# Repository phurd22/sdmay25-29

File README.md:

# Atanasoff-Berry Computer with Modern Technology

Developed by ABCm Development Group (formerly SDMAY25-29 Senior Design) under Dr. Alexander Stoytchev, the ABCm is a modern reimagining of the orignal Atanasoff-Berry Computer.

Built by Dr. Atanasoff and Clifford Berry in 1939, the Atanasoff Berry Computer (ABC) was the first digital electronic computer ever built, and the ABCm seeks to recreate the magic of this device using modern technology and design techniques. This repository houses all the final materials of the project including KiCAD projects, microcontroller and Android scripts, and supplemental documentation.

Orignal information regarding the ABCm project can be found on the [Senior Design website](https://sdmay25-29.sd.ece.iastate.edu/).

## Who are we?

The ABCm Development Group spun off from Iowa State University.  During the 2024-2025 academic year, an Electrical and Computer Engineering (ECpE) Senior Design project was proposed by Dr. Alexander Stoytchev to research the ABC and design a modern equivalent in both hardware and software.

The members of the ABCm Development Group are listed in the included [AUTHORS](./AUTHORS) file.

## Licensing

Hardware, including printed circuit board designs, CAD files, and relevant files, is licensed under [CERN-OHL-P v2](https://cern.ch/cern-ohl).

Logo and relevant components are restricted for use by the ABCm Development Group (see [Branding License and Terms](branding/LICENSE)).

All other source files and documentation herein are licensed under MIT License in their respective folders.

## Repo Guide

- The base-2 and base-10 Android punch card apps are under the 'Android Apps' folder.
- ESP32 scripts can be found under 'ESP32 Development'.
- A simulation of the ABC's control panel and Gaussian elimination algorithm are found under 'Java'.
- A simulation of the ABC in Quartus Prime can be found in 'Quartus Prime Projects'.
- A simulation of the ABC in Java can be found under 'abc-emulator'.
- Our KiCad projects are found in the folder 'KiCadProjects'. Note: these weren't used in our final implementation.
- A punch card generating program can be found under 'Decimal to Binary Page Generator'.
- Various notes on the specific modules are under 'Adder-Subtractor' and 'Base Converter'.

## GitHub Action to compile KiCad files

This repo contains an example custom PCB designed in KiCAD 5 with settings appropriate for PCB manufacture and assembly by JLCPCB. It also contains a GitHub workflow that generates the files needed by JLCPCB: gerbers, BOM, & position file. The workflow additionally generates a manual order BOM,  interactive BOM, and PDF export of the schematic. The manual order BOM includes components in the schematic not assembled by JLCPCB, such as board components not available through JLCPCB, enclosure, hardware, etc. The interactive BOM is an html document that assists in identifying component locations on the PCB for manual assembly.

## Setup Repository GitHub Actions Permissions

The workflow requires read/write access to the new repository to execute successfully.

In the new repository navigate to ```Settings```, and open the ```Actions``` > ```General``` page.

In the ```Workflow permissions``` section select ```Read and write permissions```

## New Repository Cleanup

The newly created repository will include the ```Example_Design``` example PCB design from the template repo. Files for this need to be removed and files for the new design need created. This is best done in a local clone of the new repository on your PC.

Using your Git client (Fork, GitHub Desktop, etc.) clone your new repository to a local folder on your PC.

Eventually this file, ```README.md```, should be replaced/updated with details for the new project. Consider keeping the ```Placing Orders``` and ```Failed Workflow Troubleshooting``` sections so instructions for ordering the design and troubleshooting workflow issues are readily available.

Update ```description``` and ```ownership``` entries in ```APM.yml```.

## New KiCAD Project Creation

Open the KiCAD 8 application.

In the KiCAD Project Manager select ```File``` > ```New``` > ```Project```.

In the ```Create New Project``` dialog check the box for ```Create a new directory for the project```. (Missing this step will break the GitHub workflow functionality.)

Navigate to the ```KiCadProjects``` folder under your cloned repository directory, Enter a name for your KiCAD project, and select ```Save```.

## KiCAD Schematic Setup

The GitHub workflow requires additional schematic symbol fields beyond the KiCAD defaults.

In the KiCAD schematic editor (Eeschema) select ```Preferences``` > ```Preferences...```

In the ```Eeschema``` > ```Field Name Templates``` section add the following entries:

- Part No
- Link
- LCSC
- Note

Check the ```URL``` box for the Link field.

This will add the above fields to every new symbol added to the schematic.

Note: These are KiCAD application settings and apply across all projects. If multiple users are contributing to the design, they will each need to apply these settings.

These fields can also be added to all current components in the KiCAD schematic editor under ```Tools``` > ```Edit Symbol Fields...```

For each component in the schematic either LCSC, for parts to be assembled by JLCPCB, or Part No, for parts to not be assembled by JLCPCB, must be filled out. Additionally the fields Link & Note can be filled out to provide additional information in the manually ordered parts BOM for parts to not be assembled by JLCPCB.

## KiCAD PCB Setup

The PCB design needs to be setup to match the capabilities of JLCPCB. These settings can be copied from the ```Example_Design``` in the template repo.

In the KiCAD PCB editor (PCBNew) select ```File``` > ```Board Setup...```

In the bottom left of the ```Board Setup dialog```, select ```Import Settings...```

In the bottom left of the ```Import Settings``` dialog click ```Select All```.

In the ```Import from``` field navigate to the folder ```KiCadProjects\Example_Design``` under your cloned repository directory and select ```Example_Design.pro```.

Select ```Import Settings```.

## Setup For Multiple Boards

Projects with more than one PCB, for example a motherboard and one or more daughter boards are supported. Follow the steps under ```New KiCAD Project Creation```, ```KiCAD Schematic Setup```, & ```KiCAD PCB Setup``` to create and setup a separate KiCad project for each board.

## Remove Example Design KiCad Project

After setting up the new KiCad project(s), the Example_Design files are no longer needed and the ```KiCadProjects\Example_Design``` folder can be deleted.

## Selecting Parts For JLCPCB Assembly

JLCPCB's parts catalog can be accessed at [jlcpcb.com/parts](https://jlcpcb.com/parts).

Prior to selecting parts for JLCPCB assembly it is recommended to review JLCPCB's PCB Assembly FAQs [Part 1](https://jlcpcb.com/help/article/98-pcb-assembly-faqs) & [Part 2](https://jlcpcb.com/help/article/39-pcb-assembly-faqs-part-2). Pay specific attention to the section related to Basic vs. Extended parts and the section related to polarity of components.

Recommended part selection priorities should be:

- Only SMD parts if possible (Avoid hand assembly & hand soldering fees)
- Prefer Basic parts vs. Extended parts (Avoid additional setup fees)
- Prefer parts with large inventories ( Avoid pre-order process. See ```NOTE``` under ```Placing Orders``` )

Once a part is selected enter the JLCPCB Part # in the LCSC field of the component in the KiCAD schematic.

## Notes on Footprint Rotation

JLCPCB uses the orientation of the component in the tape & reel when the feed direction is up as the zero degree reference. ( See JLCPCB's PCB Assembly FAQ [Part 2](https://jlcpcb.com/help/article/39-pcb-assembly-faqs-part-2). ) KiCAD uses the footprint orientation as the zero degree reference. For many standard component packages, common tape & reel orientations do not match the standard KiCAD footprint orientations. However, the position file generation tool of the GitHub workflow applies corrections for several standard packages to address this. ( See the internal list of rotations at the end of the [Notes about the position file](https://github.com/INTI-CMNB/KiBot#notes-about-the-position-file) section in the KiBot documentation. )

Consider an example design using an SOIC-8 component oriented with pin 1 at the top right. JLCPCB's PCB Assembly FAQ [Part 2](https://jlcpcb.com/help/article/39-pcb-assembly-faqs-part-2) indicates that for On Semiconductors SOIC-8 packages JLCPCB's zero orientation has pin 1 at the bottom-left, which would require a rotation of 180° to put pin 1 at the top-right.

KiCAD's default SOIC-8 footprint, ```SOIC-8_3.9x4.9mm_P1.27mm```, has pin 1 at the top-left. The footprint would be rotated 270° to put pin 1 at the top-right.

The footprint name, ```SOIC-8_3.9x4.9mm_P1.27mm```, matches the ```^SOIC-``` line in the internal list of rotations which adds 270° to the KiCAD rotation. This results in a total rotation of 180° in the position file, which matches the rotation expected by JLCPCB.

## Placing Orders

Prior to preparing to place orders, be sure all design changes are committed and pushed to the GitHub repository.

To generate files required for ordering parts navigate to the ```Issues``` page of the Github repository, and select ```New issue```.

To the right of ```Order and Assembly Files Request``` select ```Get started```.

Replace the ```[Your descriptor here]``` text in the title with a descriptor for your order. The beginning of the title must remain as ```Order and Assembly Files Request:``` in order to be processed.

Enter the quantity of boards you plan to order.

If applicable, select a board variant.

Select ```Submit new issue```.

A new run of the ```Process Order and Assembly Files Request``` workflow will be initiated. After a few minutes the run should complete. If successful the workflow run will add a comment with a link to the workflow run and close the issue. Open the workflow run to access the generated files. The workflow run can also be found under the repository's ```Actions``` page. The workflow run will have the same title as the requesting issue.

At the bottom of the workflow run page is a list of links to the generated files. Selecting ```Manual_Order_and_Assembly_Files``` will download a zip of the manual order BOM, interactive BOM, and schematic. Selecting ```JLCPCB_Files``` will download a zip file of the files needed for the JLCPCB order. These zip files will contain a subfolder for each KiCad project under ```KiCadProjects```.

```NOTE:``` If required parts are not in stock at JLCPCB you will need to use their pre-order process. Before ordering the PCB, parts not in JLCPCB's inventory must be ordered to your personal JLCPB parts library. When ordering these parts the initial price paid is an estimate. The parts will then be quoted. If the quote is less than the estimate the difference will be refunded. If the quote is greater than the estimate a supplemental payment must be made for the difference. The parts will then be purchased and delivered to your parts library at JLCPCB. Once all  parts are in JLCPCB's inventory or your parts library the PCB can be ordered. See [this](https://jlcpcb.com/help/article/49-how-to-build-your-own-parts-library-in-jlcpcb) JLCPCB help article for further details.

## Failed Workflow Troubleshooting

If the workflow run fails, showing a red X icon instead of a green check icon, first verify the request was filled out properly. Second look if the electrical rules check (ERC) and/or design rules check (DRC) failed. These workflow steps perform the same checks as the KiCAD schematic editor (Eescheema) for ERC and PCB editor (PCBNew) for DRC. Run these in the applications and clear all errors before proceeding.

The most common ERC error is a not driven pin error. Pins that have their ```Electrical type``` set as ```Power input``` such as power and ground pins, including the ```GND``` symbol must be connected to a pin with an ```Electrical type``` of ```Power output```. Often the symbol/pin where power & ground are supplied is a generic connector without a ```Power output``` pin. The ```PWR_FLAG``` symbol can be added to the schematic in these locations to clear this error.

## Board Variants

In certain cases it is desirable to have variability within a PCB design. Components may be added, excluded, or substituted as needed to meet various design needs. Variants can be supported through additional fields in the KiCAD schematic and minor modification of the GitHub workflow files.

NOTE: If variants are used by more than one KiCad project in the repo they must be common. When generating order files only one variant can be selected. Any project that does not have the selected variant defined will use the default variant.

### Defining Board Variants

Each board variant is identified by two unique names. One is the name used within KiCAD documents. The other is the name used by the GitHub workflow. These can (but, don't need to) be the same name. Two .yaml files in the repository need modification to define a new variant: ```Config.kibot.yaml``` and ```.github/ISSUE_TEMPLATE/Order_and_Assembly_Files_Request.yaml```.

In ```Config.kibot.yaml``` find the section below

```yaml
variants:
  - name: 'Default'
    comment: 'No variant applied'
    type: kibom
    pre_transform: '_rot_footprint'
```

The ```'Default'``` variant is already defined. This variant does not have any components added, excluded, or substituted. For each new variant add lines similar to below after the ```'Default'``` variant.

```yaml
  - name: 'Low_Spec_Variant'    # Workflow name of variant.
    comment: 'Feature reduced version of design'    # Short description of variant.
    type: kibom    # Do not change this.
    file_id: _Low_Spec    #Suffix included in filename for files generated with this variant.
    variant: Low_Spec    #KiCAD name of variant.
    pre_transform:    # Do not change these.
      - '_var_rename'
      - '_rot_footprint'
```

Insure ```- name``` of the new variant is indented the same as ```- name``` of the default variant and all indentation relative to ```- name``` is maintained as shown here.

Set ```name```, ```comment```, ```file_id```, and ```variant``` to appropriate values. Only ```comment``` may include spaces.

In ```.github/ISSUE_TEMPLATE/Order_and_Assembly_Files_Request.yaml``` find the section below

```yaml
  - type: dropdown
    id: Board_Variant
    attributes:
      label: 'Board_Variant'
      multiple: false
      options:
        - 'Default'
```

For each new variant add a line consisting of '```- [Workflow Name of Variant]```' below and at the same indentation lavel as ```-'Default'``` where ```[Workflow Name of Variant]``` matches the value of ```name``` that was entered in ```Config.kibot.yaml```.

For example, ```- 'Low_Spec_Variant'```

### Adding / Excluding Components In Variants

For any component that is added or excluded from any specific variants, add a field named Config to the symbol in the KiCAD schematic. To add a component to a specific variant enter ```+[KiCAD Name of Variant]``` in the Config field. To remove a component from a specific variant enter ```-[KiCAD Name of Variant]``` in the Config field. If a component is added or removed from multiple variants they can each be added separated by a comma.

For example if R1 should be present in the ```Default``` variant, but not in ```VariantOne``` or ```VariantTwo``` and R2 should be present only in ```VariantTwo``` then the Config field for the two components should be:

|Reference|Config|
|---|---|
|R1|-VariantOne, -VariantTwo|
|R2|+VariantTwo|

### Replacing Components In Variants

To replace a component the default and substituted part(s) must share a common schematic symbol and footprint. The substituted part will have different values for fields like: Value, Part No, LCSC and possibly others. This is accomplished by adding a new field which is named as ```[KiCAD Name of Variant]```:```[Name of Field To Replace]```. A component may have the same or different substituted parts for each variant.

For example if D1 is a green LED with a JLCPCB part # of C2297 and is to be replaced with a red LED with a JLCPCB Part # of C84256 in variant Red_LED, or a yellow LED with a JLCPCB Part # of C2296 in variant Yellow_LED, then the LCSC field would have a value of C2297. Additional fields RED_LED:LCSC with a value of C84256 and Yellow_LED:LCSC with a value of C2296 would be added.

|Reference|LCSC|Red_LED:LCSC|Yellow_LED:LCSC|
|---|---|---|---|
|D1|C2297|C84256|C2296|

## Credits

The GitHub workflow in this repository relies on the KiBot project. [INTI-CMNB/KiBot](https://github.com/INTI-CMNB/KiBot)

## Useful References

KiCAD Tutorial: [Intro to KiCAD - YouTube](https://www.youtube.com/playlist?list=PLEBQazB0HUyR24ckSZ5u05TZHV9khgA1O)

JLCPCB Parts Catalog: [jlcpcb.com/parts](https://jlcpcb.com/parts)

JLCPCB Help Articles: [jlcpcb.com/help/catalog](https://jlcpcb.com/help/catalog)

KiBot GitHub Page [INTI-CMNB/KiBot](https://github.com/INTI-CMNB/KiBot)

easyeda2kicad GitHub Page [easyeda2kicad.py](https://github.com/uPesy/easyeda2kicad.py)

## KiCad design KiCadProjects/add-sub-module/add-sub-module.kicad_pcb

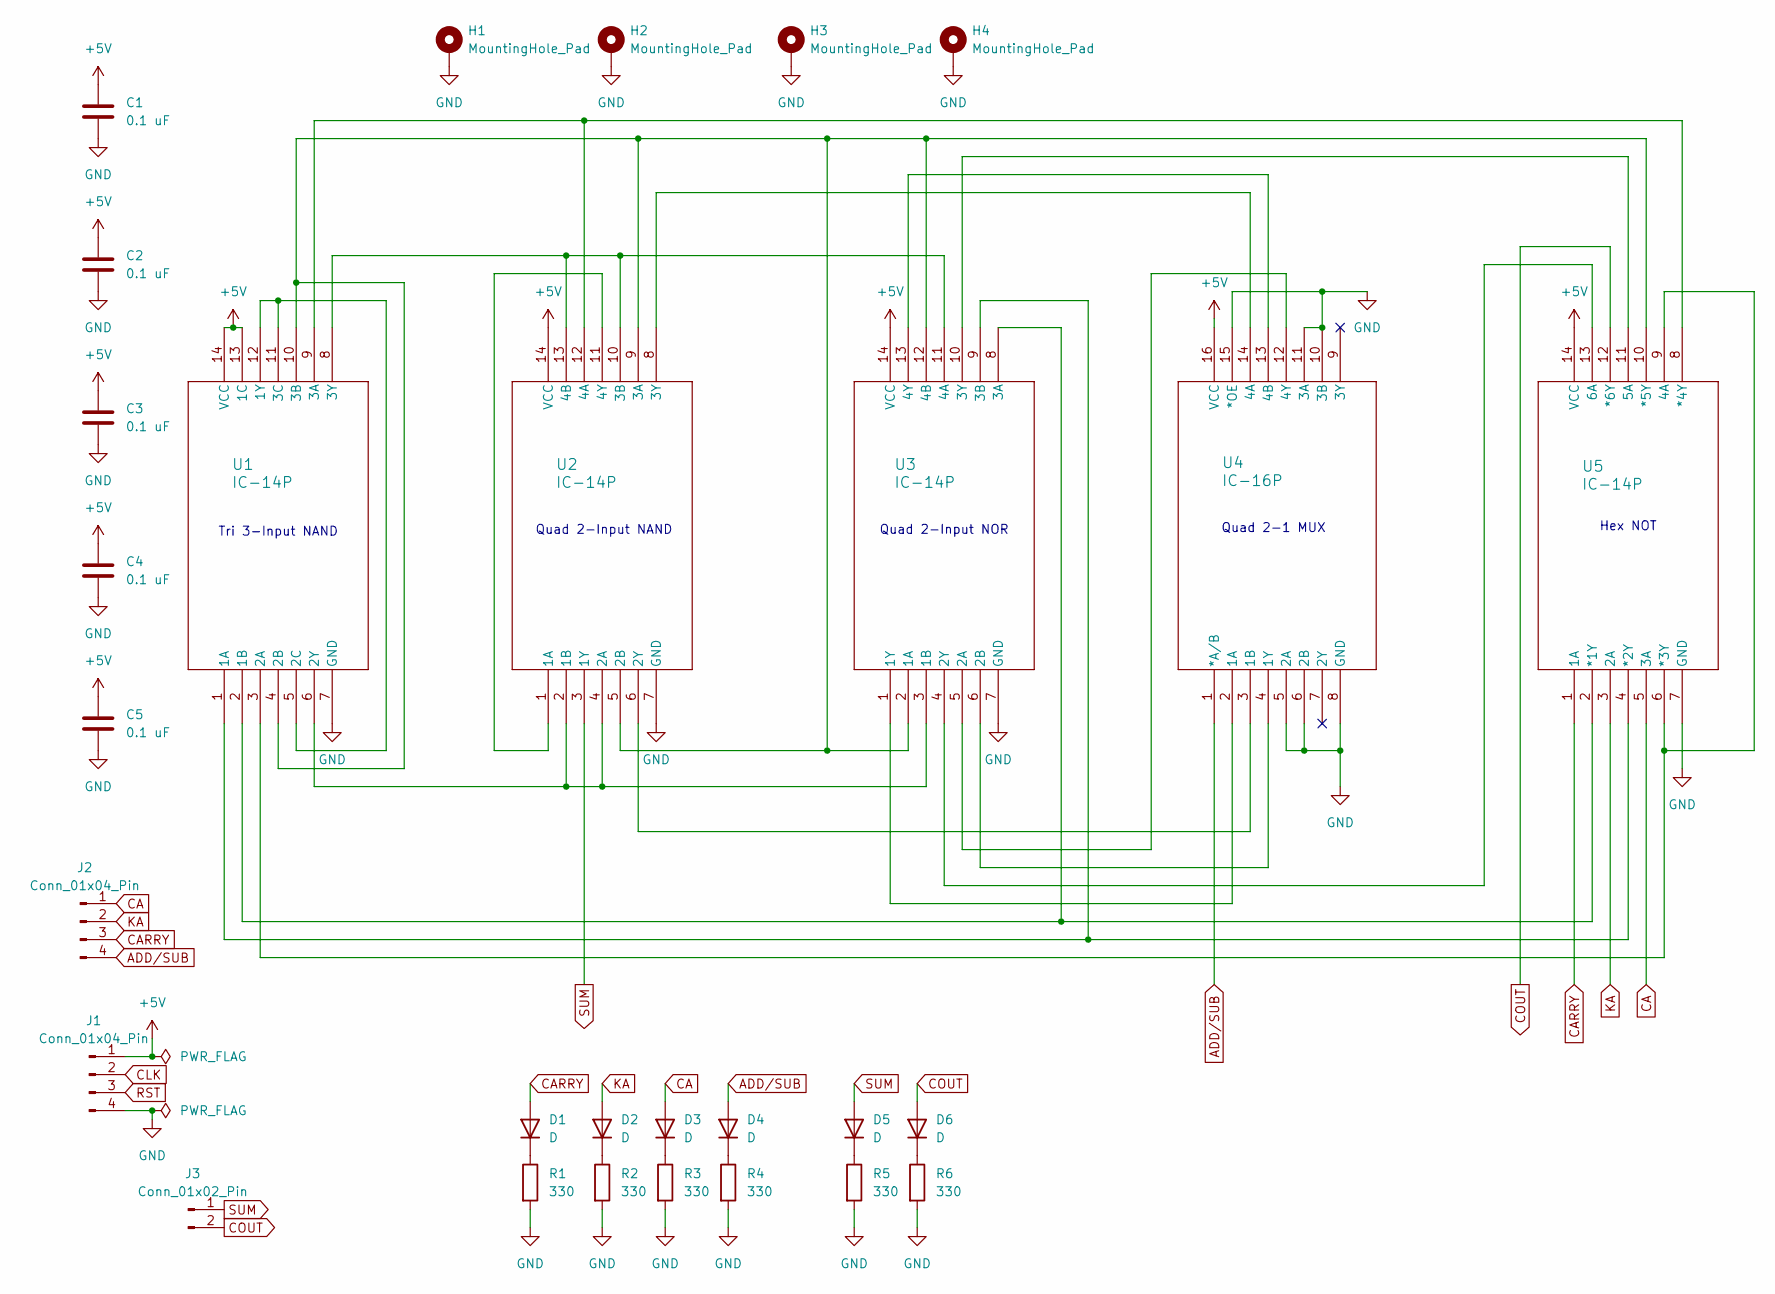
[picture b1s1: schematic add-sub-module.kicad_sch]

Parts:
C1, C2, C3, C4, C5: 0.1 uF; C_Disc_D5.0mm_W2.5mm_P5.00mm; Part No C2761729; LCSC C2761729
D1, D2, D3, D4: D; LED_D5.0mm; Part No C779442; LCSC C779442
D5, D6: D; LED_D5.0mm; Part No C779439; LCSC C779439
H1, H2, H3, H4: MountingHole_Pad; MountingHole_3.2mm_M3_DIN965_Pad
J1, J2: Conn_01x04_Pin; PinHeader_1x04_P2.54mm_Vertical; Part No C2691448; LCSC C2691448
J3: Conn_01x02_Pin; PinHeader_1x02_P2.54mm_Vertical; Part No C492401; LCSC C492401
R1, R2, R3, R4, R5, R6: 330; R_Axial_DIN0207_L6.3mm_D2.5mm_P7.62mm_Horizontal; Part No C2935230; LCSC C2935230
U1, U2, U3, U5: IC-14P; DIP-14_W7.62mm_Socket; Part No C2325; LCSC C2325
U4: IC-16P; DIP-16_W7.62mm_Socket; Part No C2326; LCSC C2326

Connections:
+5V: C1.1, C2.1, C3.1, C4.1, C5.1, J1.1, U1.13 (1C), U1.14 (VCC), U2.14 (VCC), U3.14 (VCC), U4.16 (VCC), U5.14 (VCC)
ADD/SUB: D4.2 (A), J2.4, U4.1 (*A/B)
CA: D3.2 (A), J2.1, U5.5 (3A)
CARRY: D1.2 (A), J2.3, U5.1 (1A)
CLK: J1.2
COUT: D6.2 (A), J3.2, U5.12 (*6Y)
GND: C1.2, C2.2, C3.2, C4.2, C5.2, H1.1, H2.1, H3.1, H4.1, J1.4, R1.2, R2.2, R3.2, R4.2, R5.2, R6.2, U1.7 (GND), U2.7 (GND), U3.7 (GND), U4.5 (2A), U4.6 (2B), U4.8 (GND), U4.10 (3B), U4.11 (3A), U4.15 (*OE), U5.7 (GND)
KA: D2.2 (A), J2.2, U5.3 (2A)
unnamed: D1.1 (K), R1.1
unnamed: D2.1 (K), R2.1
unnamed: D3.1 (K), R3.1
unnamed: D4.1 (K), R4.1
unnamed: D5.1 (K), R5.1
unnamed: D6.1 (K), R6.1
unnamed: U1.1 (1A), U3.9 (3B), U5.4 (*2Y)
unnamed: U1.2 (1B), U3.8 (3A), U5.2 (*1Y)
unnamed: U1.5 (2C), U1.11 (3C), U1.12 (1Y)
unnamed: U1.3 (2A), U5.6 (*3Y), U5.9 (4A)
unnamed: U1.4 (2B), U1.10 (3B), U2.5 (2B), U2.9 (3A), U3.2 (1A), U3.12 (4B), U5.10 (*5Y)
unnamed: U1.6 (2Y), U2.2 (1B), U2.4 (2A), U3.3 (1B)
unnamed: U1.9 (3A), U2.12 (4A), U5.8 (*4Y)
unnamed: U1.8 (3Y), U2.10 (3B), U2.13 (4B), U3.11 (4A)
unnamed: U2.1 (1A), U2.11 (4Y)
unnamed: U2.6 (2Y), U4.3 (1B)
unnamed: U2.8 (3Y), U4.14 (4A)
unnamed: U3.1 (1Y), U4.2 (1A)
unnamed: U3.5 (2A), U4.12 (4Y)
unnamed: U3.6 (2B), U4.4 (1Y)
unnamed: U3.4 (2Y), U5.13 (6A)
unnamed: U3.10 (3Y), U5.11 (5A)
unnamed: U3.13 (4Y), U4.13 (4B)
RST: J1.3
SUM: D5.2 (A), J3.1, U2.3 (1Y)

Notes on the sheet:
Tri 3-Input NAND
Quad 2-Input NOR
Hex NOT
Quad 2-Input NAND
Quad 2-1 MUX

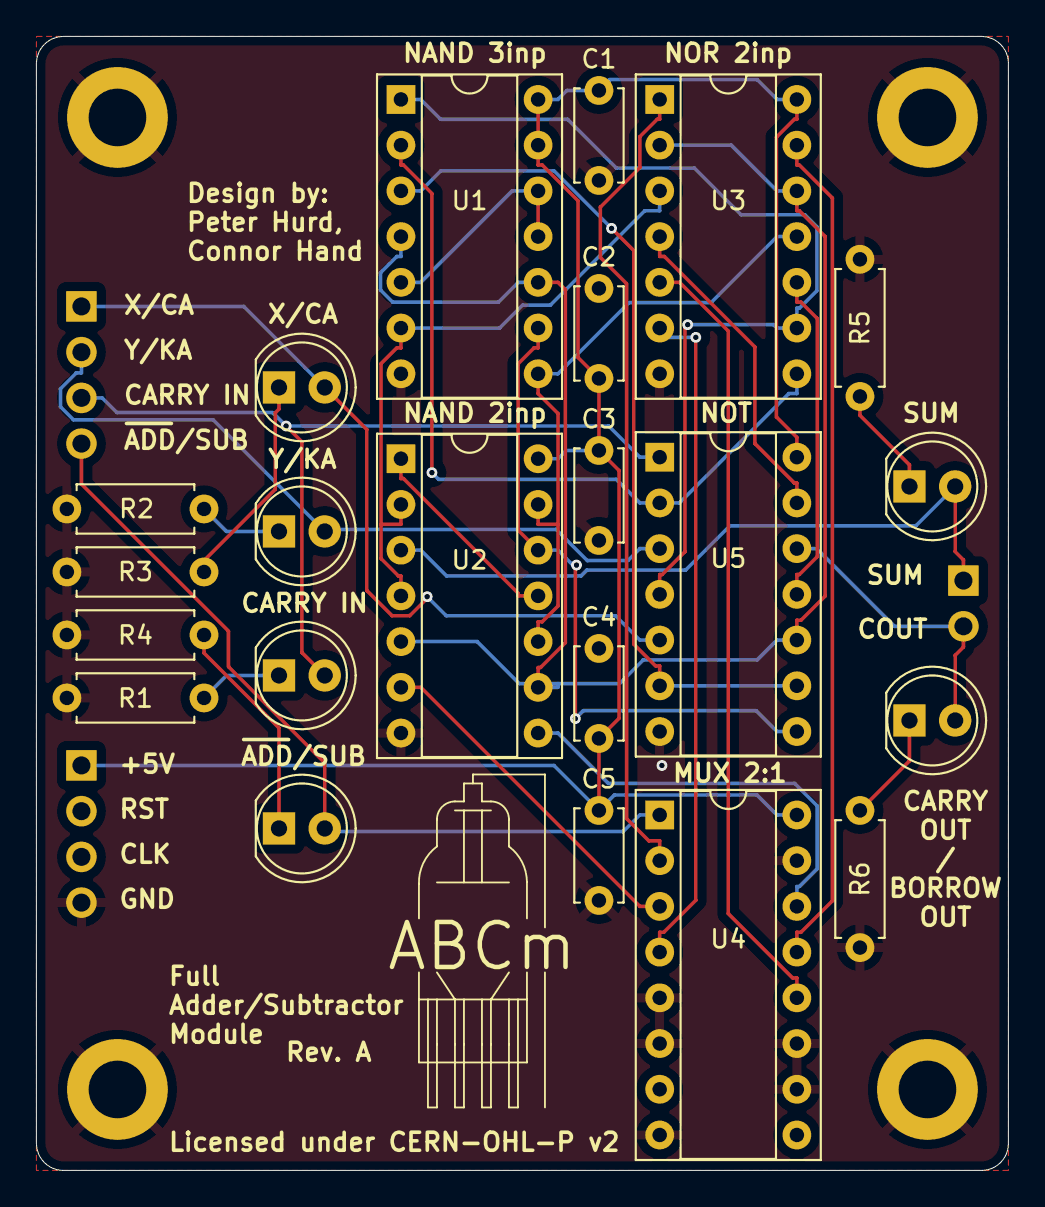
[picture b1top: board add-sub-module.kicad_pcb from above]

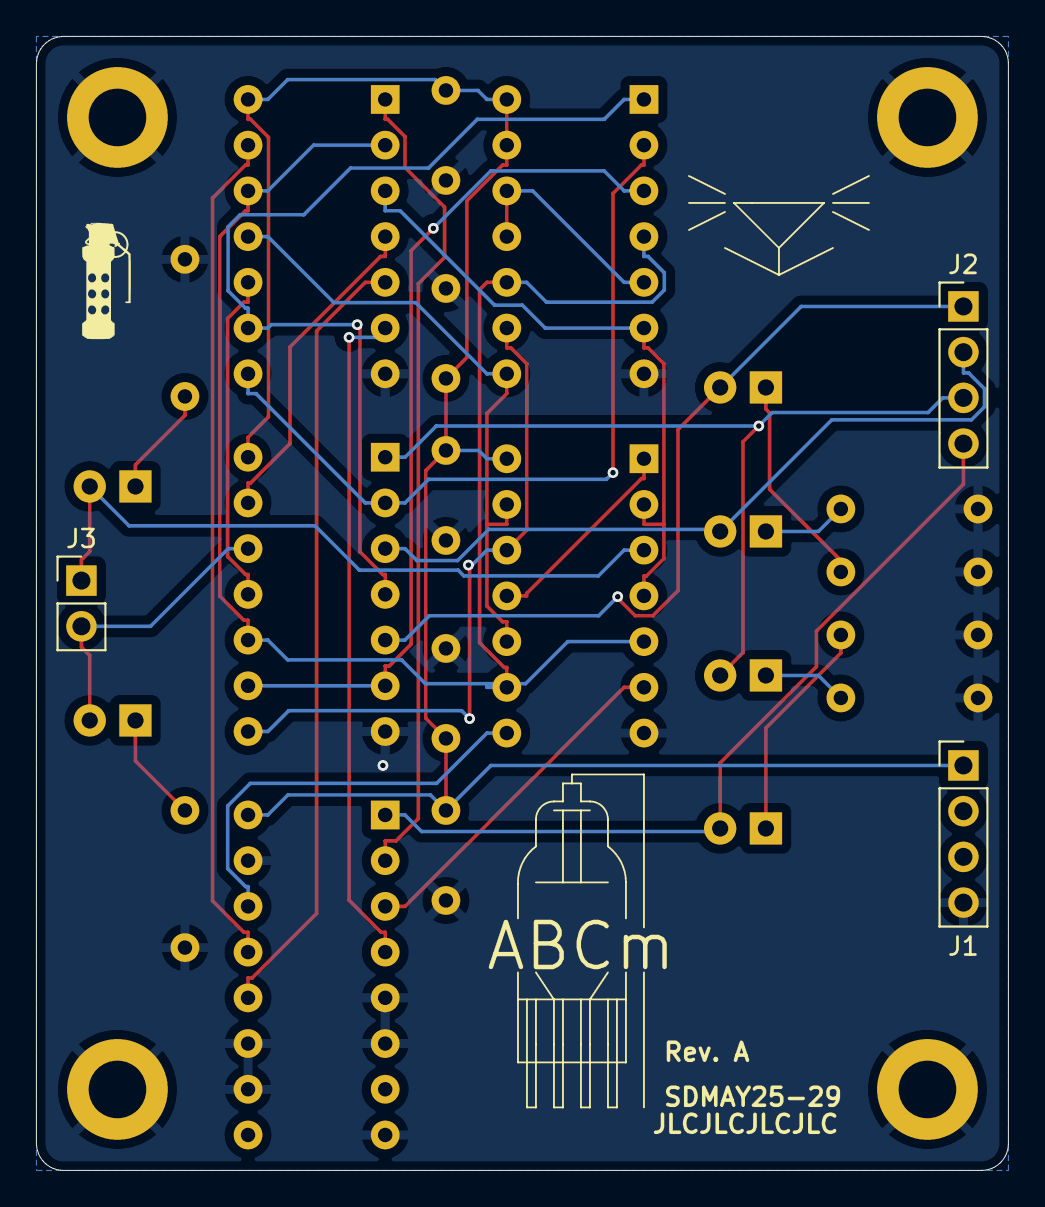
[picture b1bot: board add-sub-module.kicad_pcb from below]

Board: 2 copper layers, 54.0 x 63.0 mm, 31 parts (4 on the bottom side), 31 nets.

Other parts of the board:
Logo1, Logo2: logo

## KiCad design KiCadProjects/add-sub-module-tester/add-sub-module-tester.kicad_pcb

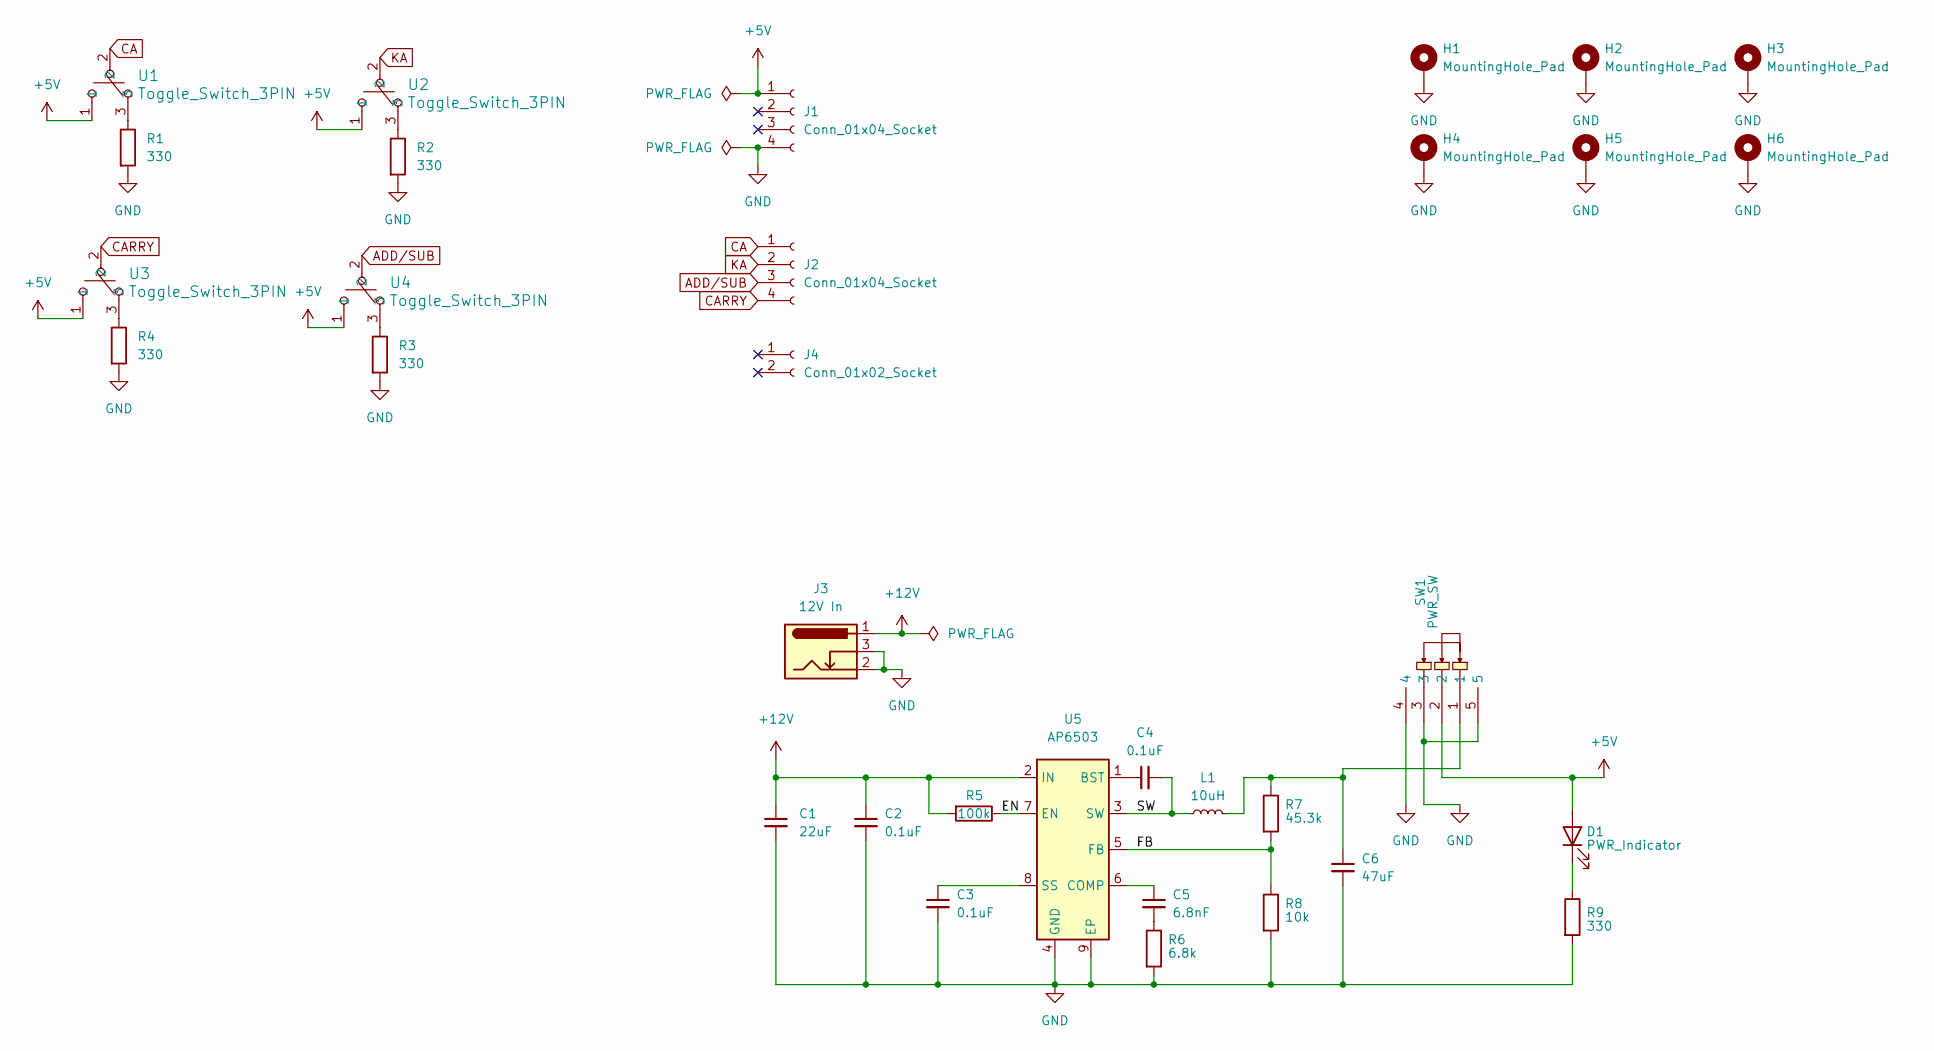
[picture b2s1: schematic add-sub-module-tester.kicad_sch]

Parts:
C1: 22uF; CP_Elec_5x5.4; Part No C239256; LCSC C239256
C2, C3, C4: 0.1uF; C_0603_1608Metric_Pad1.08x0.95mm_HandSolder; Part No C14663; LCSC C14663
C5: 6.8nF; C_0603_1608Metric_Pad1.08x0.95mm_HandSolder; Part No C1631; LCSC C1631
C6: 47uF; CP_Elec_6.3x7.7; Part No C72523; LCSC C72523
D1: PWR_Indicator; LED_0603_1608Metric_Pad1.05x0.95mm_HandSolder; Part No C125098; LCSC C125098
H1, H2, H3, H4, H5, H6: MountingHole_Pad; MountingHole_3.2mm_M3_DIN965_Pad
J1, J2: Conn_01x04_Socket; PinSocket_1x04_P2.54mm_Vertical; Part No C541851; LCSC C541851
J3: 12V In; BarrelJack_Horizontal; Part No C136744; LCSC C136744
J4: Conn_01x02_Socket; PinSocket_1x02_P2.54mm_Vertical; Part No C49661; LCSC C49661
L1: 10uH; L_Coilcraft_LPS5030; Part No C20417074; LCSC C20417074
R1, R2, R3, R4: 330; R_Axial_DIN0207_L6.3mm_D2.5mm_P7.62mm_Horizontal; Part No C2935230; LCSC C2935230
R5: 100k; R_0603_1608Metric_Pad0.98x0.95mm_HandSolder; Part No C14675; LCSC C14675
R6: 6.8k; R_0603_1608Metric_Pad0.98x0.95mm_HandSolder; Part No C114632; LCSC C114632
R7: 45.3k; R_0603_1608Metric_Pad0.98x0.95mm_HandSolder; Part No C23058; LCSC C23058
R8: 10k; R_0603_1608Metric_Pad0.98x0.95mm_HandSolder; Part No C2930027; LCSC C2930027
R9: 330; R_0603_1608Metric_Pad0.98x0.95mm_HandSolder; Part No C22104; LCSC C22104
SW1: PWR_SW; SW-TH_SK12D07VG5; Part No C431548; LCSC C431548
U1, U2, U3, U4: Toggle_Switch_3PIN; SW-TH_MT-0-103-A101-M200-RS; Part No C1788493; LCSC C1788493
U5: AP6503; Diodes_SO-8EP; Part No C51811; LCSC C51811

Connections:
+5V: D1.2 (A), J1.1, SW1.2, U1.1, U2.1, U3.1, U4.1
+12V: C1.1, C2.1, J3.1, R5.2, U5.2 (IN)
/EN: R5.1, U5.7 (EN)
/FB: R7.2, R8.1, U5.5 (FB)
/SW: C4.2, L1.1, U5.3 (SW)
ADD/SUB: J2.3, U4.2
CA: J2.1, U1.2
CARRY: J2.4, U3.2
GND: C1.2, C2.2, C3.2, C6.2, H1.1, H2.1, H3.1, H4.1, H5.1, H6.1, J1.4, J3.2, J3.3, R1.2, R2.2, R3.2, R4.2, R6.2, R8.2, R9.2, SW1.3, SW1.4, SW1.5, U5.4 (GND), U5.9 (EP)
KA: J2.2, U2.2
unnamed: C5.2, R6.1
unnamed: C6.1, L1.2, R7.1, SW1.1
unnamed: D1.1 (K), R9.1
unnamed: R1.1, U1.3
unnamed: R2.1, U2.3
unnamed: R3.1, U4.3
unnamed: R4.1, U3.3
unnamed: C4.1, U5.1 (BST)
unnamed: C5.1, U5.6 (COMP)
unnamed: C3.1, U5.8 (SS)

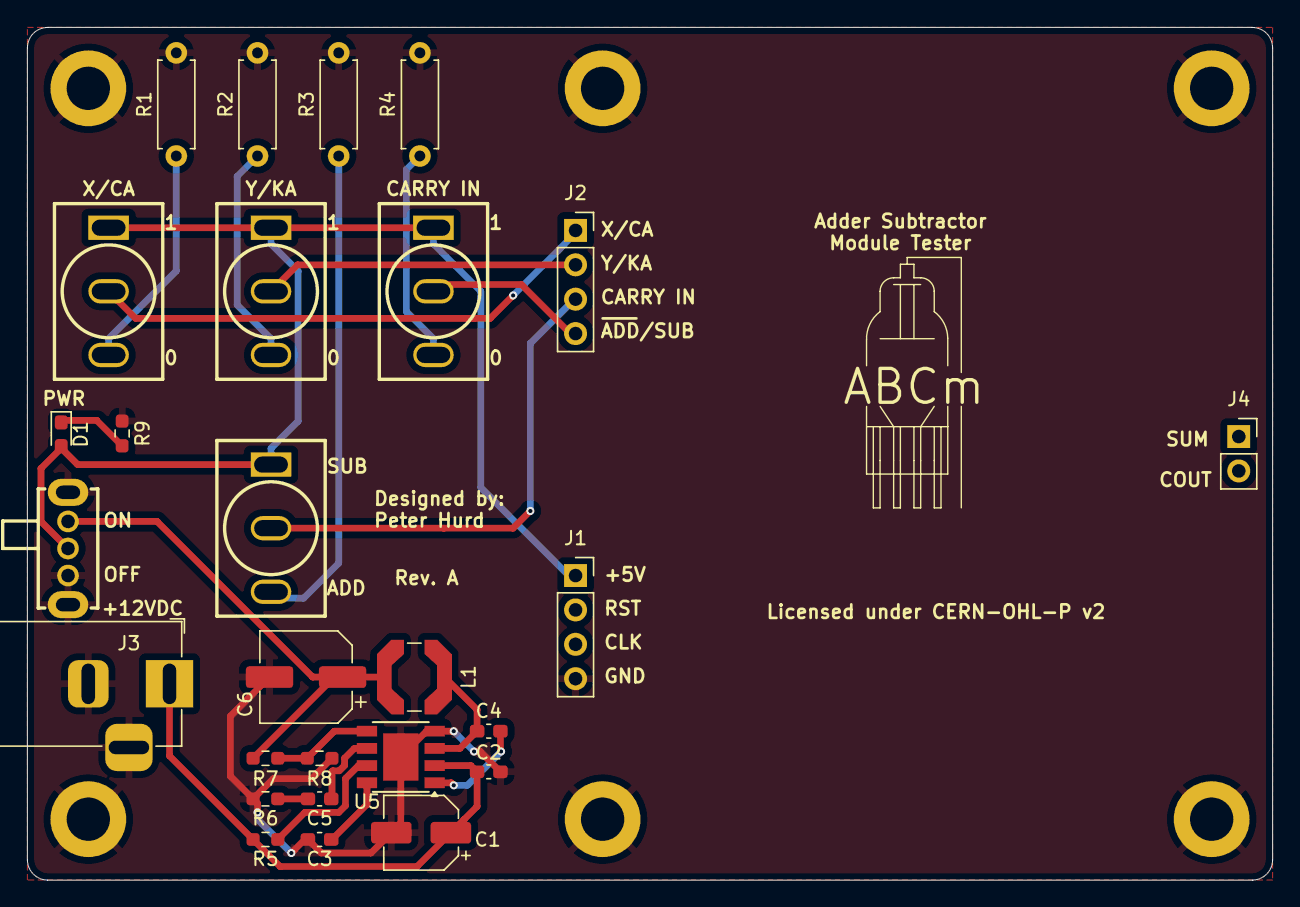
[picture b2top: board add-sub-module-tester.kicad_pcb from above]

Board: 2 copper layers, 92.0 x 63.0 mm, 35 parts (1 on the bottom side), 20 nets.

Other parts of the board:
Logo1: logo
logo2: logo

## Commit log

2024-09-25 Create GitHub actions workflow for Kicad
2024-10-02 Fix GitHub Action to compile kicad files
2024-10-15 Task Decomposition
2024-10-17 Added Adder-Subtractor folder and some notes within it.
2024-10-23 testing docker changes
2024-10-23 more docker changes
2024-10-23 still trying to get this to work
2024-10-23 still not working
2024-10-26 Adding rest of parts needed for add-sub module
2024-10-29 Working on add-sub schematic
2024-10-30 Finished add-sub schematic
2024-11-05 Added decimal to binary page generator (the one that burned holes into paper)
2024-11-06 Fixed error in explanation document
2024-11-07 Added start of base converter circuit
2024-11-12 started working on buddy app
2024-11-12 rev. v1 for add sub
2024-11-12 final rev v.1
2024-11-12 Update Dockerfile
2024-11-12 adding kibot features
2024-11-12 fix erc and drc scripts
2024-11-12 fix file generator scripts
2024-11-12 still fixing erc and drc scripts
2024-11-12 still fixing drc and erc
2024-11-12 i think i finally fixed it
2024-11-12 revert some previous changes
2024-11-12 added additional footprints to general footprint library
2024-11-13 add add sub tester
2024-11-14 made a very rough prototype for the UI
2024-11-14 finished tester design
2024-11-14 changed colors
2024-11-16 Updated links and footprints in add-subtractor schematic, also added my maker's mark
2024-11-17 Changed footprints in schematic
2024-11-17 Fixed a couple links
2024-11-19 Adding socket part numbers to ICs in schematic
2024-11-20 still need to fix traces
2024-11-21 fixed module, need work on tester
2024-11-21 Added text to binary page to assist in understanding how numbers are stored
2024-11-21 still working on tester
2024-11-21 Started working on punchcard customview
2024-11-21 made some slight adjustments
2024-11-22 initial updates after meeting
2024-11-22 final updates for Revision A
2024-11-22 FINAL final changes for Rev. A
2024-11-22 FINAL FINAL final updates for Rev. A
2024-11-22 Rev. A v.1.2
2024-12-01 oops forgot to push this
2024-12-01 tweaked something still needs work
2024-12-05 committing in case the world ends
2024-12-05 ready for meeting. still needs a bit of ironing out but good enough for a prototype
2024-12-05 Small changes to PCB, grounded MUX OE pin and updated PCB from schematic
2025-02-05 Added folder for Arduino sketches
2025-02-06 Adding ESP32 test app
2025-02-07 Bluetooth test with Android app is working
2025-02-07 made some modifications to UI and how holes are punched
2025-02-07 Changes to color of buttons in my ESP32 bluetooth app.
2025-02-07 Base 2 punch card view is working
2025-02-07 some more changes. bugs still present
2025-02-13 Added Quartus Prime Projects folder and started AdderSubtractor project
2025-02-13 added autotext resizing, fixed leading 0 bug, added numbers to label rows)
2025-02-13 text now sticks to bottom even when it get's smaller
2025-02-13 Progress on base2 punch design
2025-02-13 Block diagram is complete
2025-02-14 Multiple pages working
2025-02-14 added projects for base conversion and timing
2025-02-14 fix annoying bug
2025-02-18 demo script for generating new eeprom data
2025-02-21 Changes to timing_module model and start on main model
2025-02-21 Added arduino sketch for testing EEPROM with ESP32
2025-02-21 created quartus holder/shifter circuit, issue present
2025-02-26 Java Gaussian programs
2025-02-26 Control Panel GUI, no operation yet
2025-02-27 Bunch of functionality, not complete yet
2025-02-27 Derived controls from ABC Manual 1968
2025-02-28 Almost done with Reading Base-10 Cards Steps
2025-02-28 started counter drum, created 4to1mux and dff bsf files
2025-02-28 Changes to app, communicating with ESP32
2025-02-28 IT WORKS
2025-03-03 implemented test circuit from Friday
2025-03-07 Added base10 ESP32 bluetooth receiver code
2025-03-07 made it possible for the base 10 punch to connect to esp32
2025-03-07 base 10 should be ready to send to ESP32 now
2025-03-07 Updated Base10BTReceiver
2025-03-07 ESP32 end is working woohoogit add .!
2025-03-07 Control Panel is better looking and adding functionality
2025-03-10 started to add base 10 conversion to Quartus main
2025-03-11 Updated Arduino base10 receiver code to match our design
2025-03-12 Added notes to ESP32 Base10Receiver
2025-03-14 updated timing module with synchronous counters and new memory to store control signals
2025-03-14 Split up Android apps
2025-03-16 Added file on wrong branch
2025-03-16 Good progress setting up BLE with ESP32S3
2025-03-16 BLE is fully functional
2025-03-17 all works
2025-03-17 Updated bluetooth methods to use BLE instead of classic bluetooth
2025-03-18 Base10 app and ESP32 arduino code work together now
2025-03-20 Split base-2 app into read and write versions
2025-03-20 Made progress for layout on read app
2025-03-22 UI looks good
2025-03-24 configured layout for tablets
2025-04-02 updates to Quartus project and base conversion kicad schematic
2025-04-03 Made Base2BTReceiver for ESP32S3
2025-04-03 Base 2 read app sends data to ESP32 now
2025-04-04 Added todo notes from meeting
2025-04-04 Added more notes
2025-04-04 Added notes for what to get done from meeting
2025-04-05 Updated bluetooth connection method
2025-04-05 Fixed direction bits were being sent
2025-04-05 Made updates to base-2 apps based on meeting with Stoytchev
2025-04-07 More java
2025-04-08 New directory and Drums
2025-04-08 AddSubMecahnism does bitwise add/sub correctly
2025-04-10 Conversion?
2025-04-11 Changed anumber
2025-04-11 Clocked microcontroller program is working
2025-04-12 Changed some preset numbers
2025-04-12 Base10BTReceiver now acts as 4 bit counter and has reset
2025-04-12 Updated app to use MAC address for bluetooth and updated button design
2025-04-16 Functionality
2025-04-17 Wrote arduino script to test sending data to Write tablet
2025-04-18 Base 2 send to write tablet working
2025-04-18 Setting up tablet to tablet data transfer... uh oh
2025-04-18 Working on TCP connection between the base-2 tablets
2025-04-21 Bunch of Base2/10 functionality
2025-04-21 added comments
2025-04-24 Modified test ardunio script for consistency
2025-04-24 Attempt at using WiFi direct
2025-04-24 Communication between apps works finally
2025-04-24 Added helpful first page
2025-04-25 Updated ESP32 Base2 Send script to work consistently. Changed inital values in Base2 Read app.
2025-04-25 Set up app for new ESP32
2025-04-26 some work done on ESP32 code
2025-04-26 Updated Base10BTReceiver Arduino Script
2025-04-27 Apps fully work woohoo
2025-04-28 Updated ESP32 scripts
2025-04-29 Added new script for binary writer ESP
2025-04-29 Finished base 2 sender script for ESP
2025-04-29 Fixed clock read bug
2025-04-29 Fixed bug related to reading counters
2025-05-02 Added comments to base-2 apps
2025-05-05 just need to add mask buttons now
2025-05-05 base-10 card app finished
2025-05-05 Fixed ESP32 programs to use 6-bit counter resetting at 59
2025-05-05 added all relevant eeprom scripts and moved to folder EEPROM Scripts
2025-05-05 Upaded base-2 sender ESP32 to go on next cycle
2025-05-06 Got a lot done today, edited ESP32 scripts to work with final design, edited EEPROM timing drum script, updated base-2 apps
2025-05-08 Added license files to Android apps and ESP32 scripts
2025-05-08 Added 3D models
2025-05-08 Added extra time for sending data between tablets
2025-05-13 Create KiCad schematics based on breadboards
2025-05-15 Added final schematic for Add Sub Logic
2025-05-15 Finalized code, needs MIT License
2025-05-15 MIT Open Source License
2025-05-15 Open source
2025-05-15 Added licensing and edited README
2025-05-15 Add branding license
